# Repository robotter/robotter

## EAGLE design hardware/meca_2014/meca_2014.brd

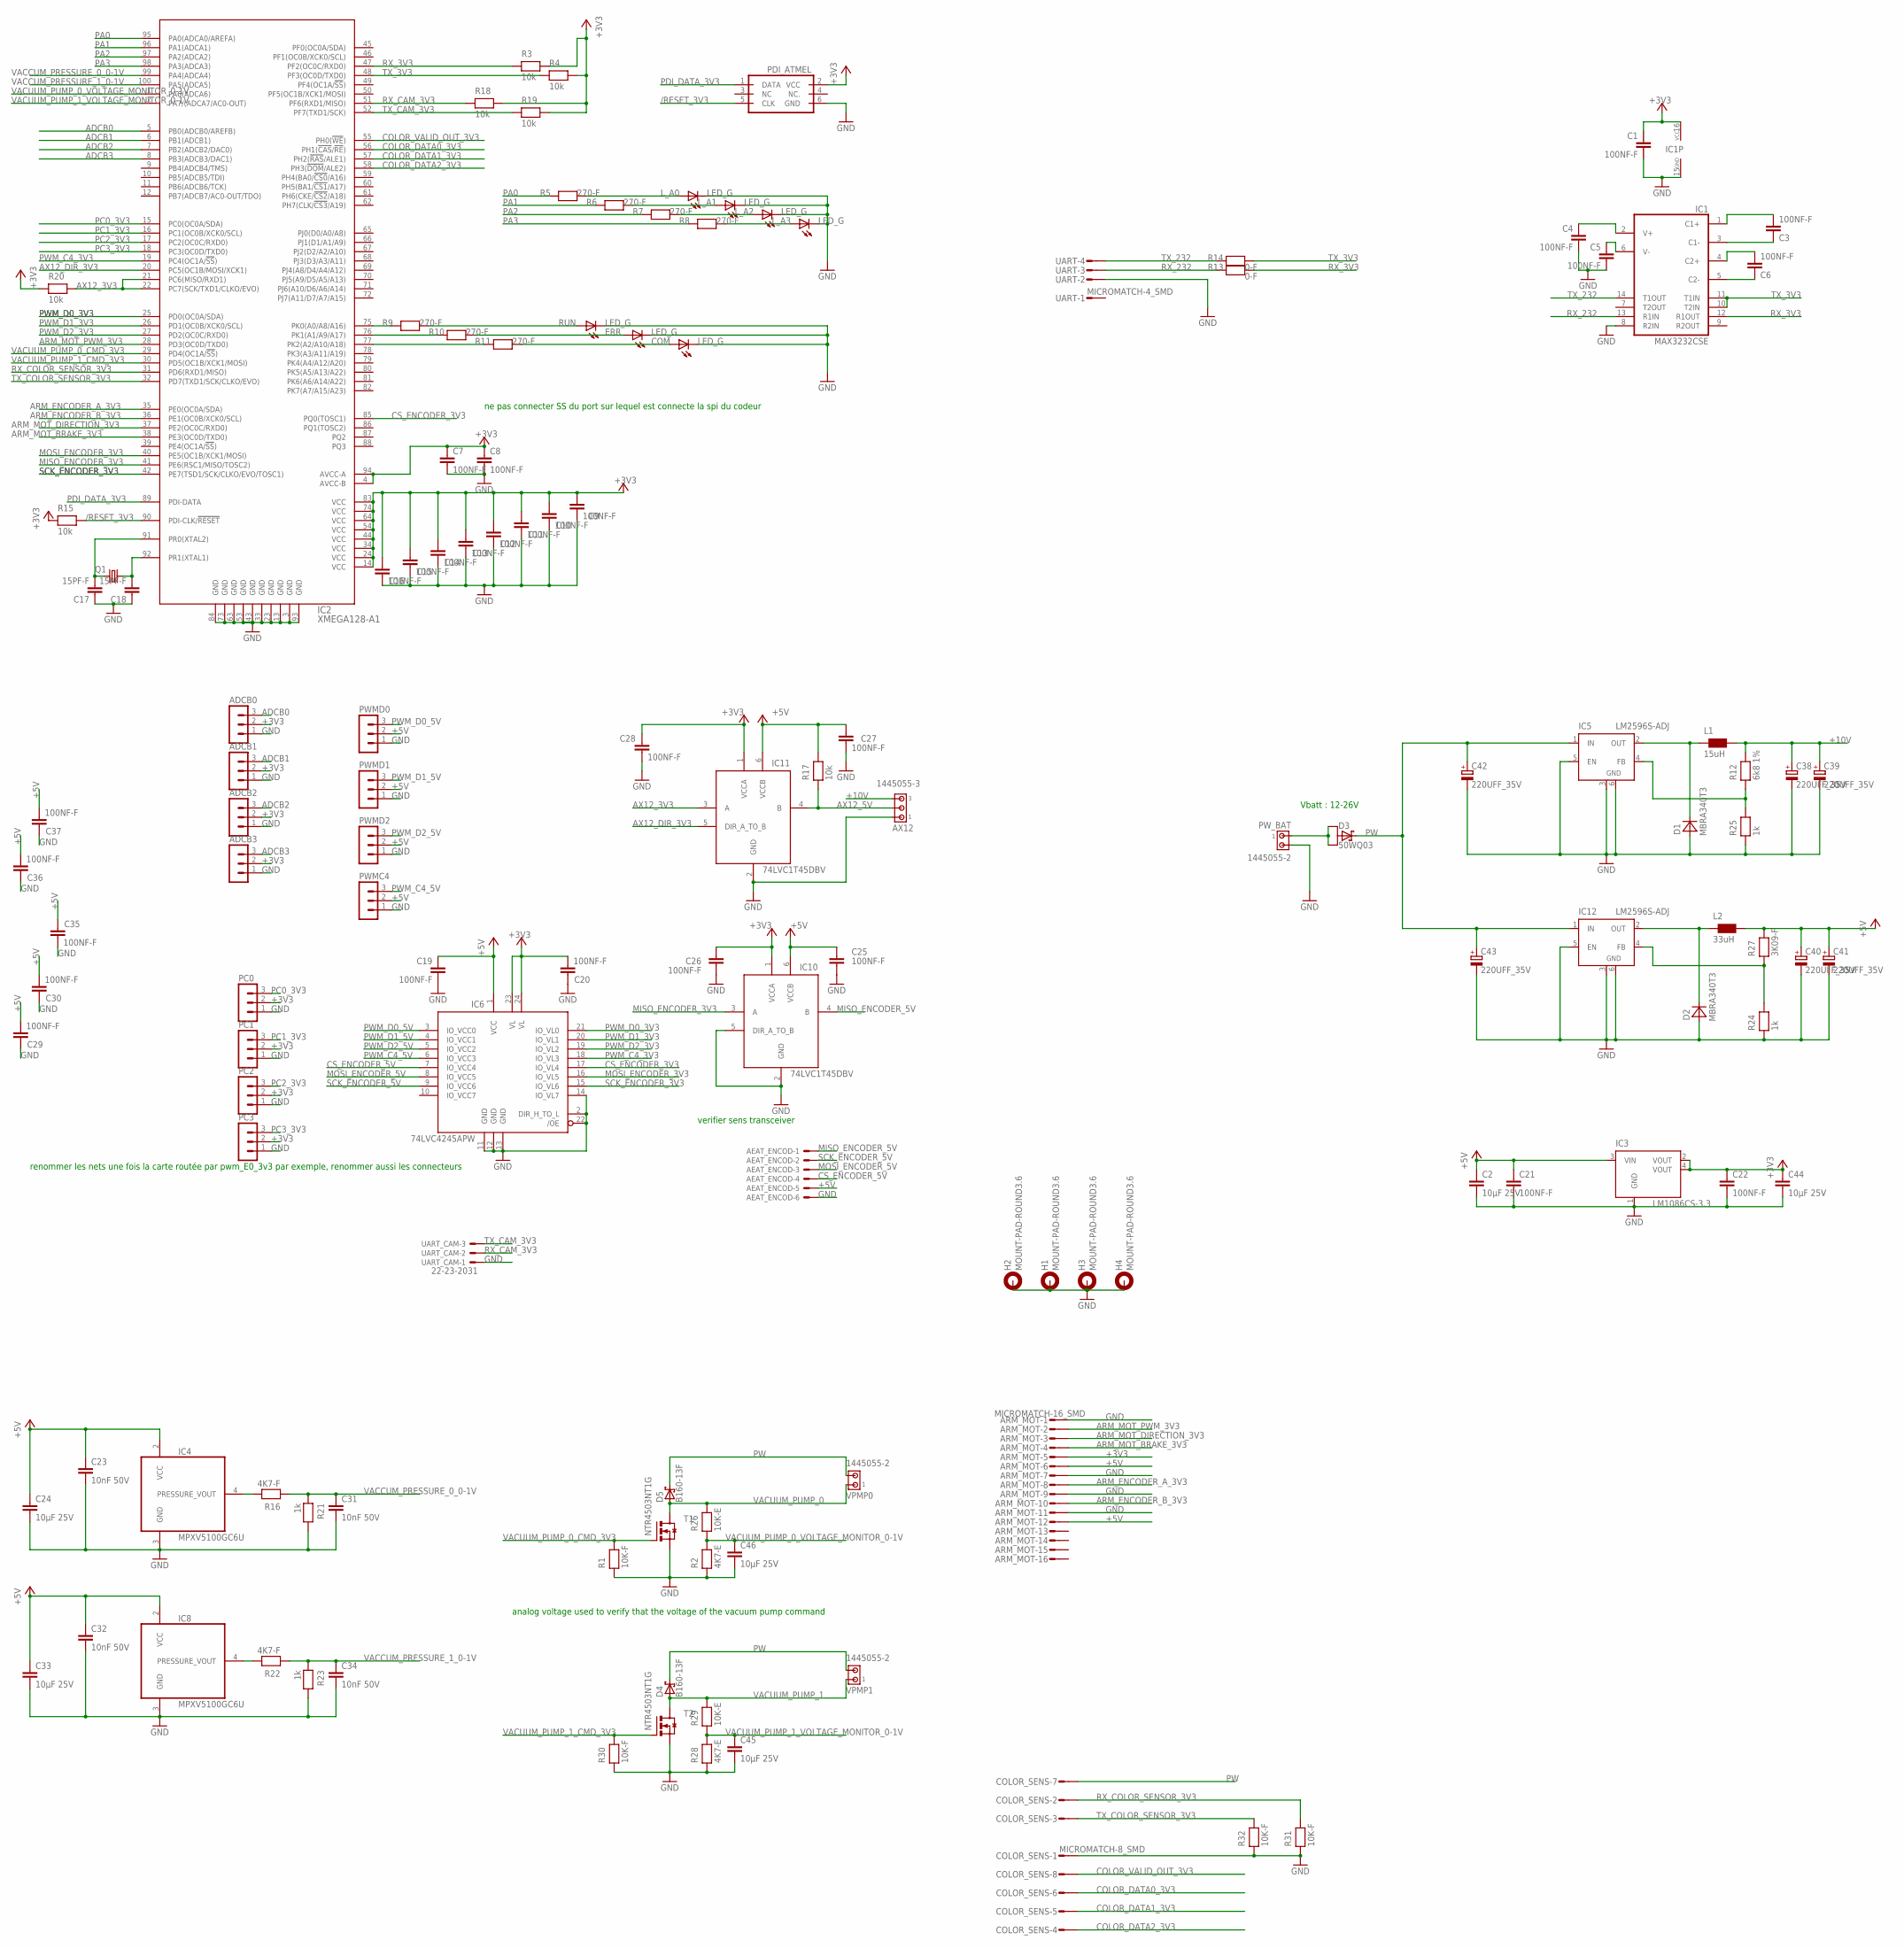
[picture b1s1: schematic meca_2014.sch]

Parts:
ADCB0, ADCB1, ADCB2, ADCB3: MA03-1
AEAT_ENCOD: 22-23-2061
ARM_MOT: MICROMATCH-16_SMD
AX12: 1445055-3
C1, C3, C4, C5, C6, C7, C8, C9, C10, C11, C12, C13, C14, C15, C16, C19, C20, C21, C22, C25, C26, C27, C28, C29, C30, C35, C36, C37: 100NF-F; C0603
C2, C24, C33, C44, C45, C46: 10µF 25V; C1210
C17, C18: 15PF-F; C0603
C23, C31, C32, C34: 10nF 50V; C0603
C38, C39, C40, C41, C42, C43: 220UFF_35V; PANASONIC_F
COLOR_SENS: MICROMATCH-8_SMD
COM: LED_G; CHIP-LED0805
D1, D2: MBRA340T3; SMA
D3: 50WQ03; TO252
D4, D5: B160-13F; SMA
ERR: LED_G; CHIP-LED0805
H1, H2, H3, H4: MOUNT-PAD-ROUND3.6; 3,6-PAD
IC1: MAX3232CSE; SO16
IC2: XMEGA128-A1; TQFP100
IC3: LM1086CS-3.3; TO263
IC4, IC8: MPXV5100GC6U; 482A
IC5, IC12: LM2596S-ADJ; TO263-5
IC6: 74LVC4245APW; TSSOP24
IC10, IC11: 74LVC1T45DBV; SOT23-6
L1: 15uH; SRR1280
L2: 33uH; SRR1280
L_A0, L_A1, L_A2, L_A3: LED_G; CHIP-LED0805
PC0, PC1, PC2, PC3: MA03-1
PDI_ATMEL: PDI_ATMELL; ML6L
PWMC4: MA03-1
PWMD0, PWMD1, PWMD2: MA03-1
PW_BAT: 1445055-2
Q1: CRYSTAL_16MHZ_HC49UP; HC49UP
R1, R30, R31, R32: 10K-F; R0603
R2, R28: 4K7-E; R0805
R3, R4, R15, R17, R18, R19, R20: 10k; R0603
R5, R6, R7, R8, R9, R10, R11: 270-F; R0603
R12: 6k8 1%; R0603
R13, R14: 0-F; R0603
R16, R22: 4K7-F; R0603
R21, R23, R24, R25: 1k; R0603
R26, R29: 10K-E; R0805
R27: 3K09-F; R0603
RUN: LED_G; CHIP-LED0805
T1, T2: NTR4503NT1G; SOT23
UART: MICROMATCH-4_SMD
UART_CAM: 22-23-2031
VPMP0, VPMP1: 1445055-2

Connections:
+3V3: ADCB0.2, ADCB1.2, ADCB2.2, ADCB3.2, ARM_MOT.5, C1.1, C7.1, C8.1, C9.1, C10.1, C11.1, C12.1, C13.1, C14.1, C15.1, C16.1, C20.1, C22.1, C26.1, C28.1, C44.1, IC1.16 (VCC), IC2.4 (AVCC-B), IC2.14 (VCC), IC2.24 (VCC), IC2.34 (VCC), IC2.44 (VCC), IC2.54 (VCC), IC2.64 (VCC), IC2.74 (VCC), IC2.83 (VCC), IC2.94 (AVCC-A), IC3.2 (VOUT), IC3.4 (VOUT), IC6.23 (VL), IC6.24 (VL), IC10.1 (VCCA), IC11.1 (VCCA), PC0.2, PC1.2, PC2.2, PC3.2, PDI_ATMEL.2 (VCC), R3.2, R4.2, R15.1, R18.2, R19.2, R20.1
+5V: AEAT_ENCOD.5, ARM_MOT.6, ARM_MOT.12, C2.1, C19.1, C21.1, C23.1, C24.1, C25.1, C27.1, C29.1, C30.1, C32.1, C33.1, C35.1, C36.1, C37.1, C40.+, C41.+, IC3.3 (VIN), IC4.2 (VCC), IC6.1 (VCC), IC8.2 (VCC), IC10.6 (VCCB), IC11.6 (VCCB), L2.2, PWMC4.2, PWMD0.2, PWMD1.2, PWMD2.2, R17.2, R27.2
+10V: AX12.3, C38.+, C39.+, L1.2, R12.2
/RESET_3V3: IC2.90 (PDI-CLK/!RESET), PDI_ATMEL.5 (CLK), R15.2
ADCB0: ADCB0.3, IC2.5 (PB0(ADCB0/AREFB))
ADCB1: ADCB1.3, IC2.6 (PB1(ADCB1))
ADCB2: ADCB2.3, IC2.7 (PB2(ADCB2/DAC0))
ADCB3: ADCB3.3, IC2.8 (PB3(ADCB3/DAC1))
ARM_ENCODER_A_3V3: ARM_MOT.8, IC2.35 (PE0(OC0A/SDA))
ARM_ENCODER_B_3V3: ARM_MOT.10, IC2.36 (PE1(OC0B/XCK0/SCL))
ARM_MOT_BRAKE_3V3: ARM_MOT.4, IC2.38 (PE3(OC0D/TXD0))
ARM_MOT_DIRECTION_3V3: ARM_MOT.3, IC2.37 (PE2(OC0C/RXD0))
ARM_MOT_PWM_3V3: ARM_MOT.2, IC2.28 (PD3(OC0D/TXD0))
AX12_3V3: IC2.21 (PC6(MISO/RXD1)), IC2.22 (PC7(SCK/TXD1/CLKO/EVO)), IC11.3 (A), R20.2
AX12_5V: AX12.2, IC11.4 (B), R17.1
AX12_DIR_3V3: IC2.20 (PC5(OC1B/MOSI/XCK1)), IC11.5 (DIR_A_TO_B)
COLOR_DATA0_3V3: COLOR_SENS.6, IC2.56 (PH1(!CAS!/!RE!))
COLOR_DATA1_3V3: COLOR_SENS.5, IC2.57 (PH2(!RAS!/ALE1))
COLOR_DATA2_3V3: COLOR_SENS.4, IC2.58 (PH3(!DOM!/ALE2))
COLOR_VALID_OUT_3V3: COLOR_SENS.8, IC2.55 (PH0(!WE!))
CS_ENCODER_3V3: IC2.85 (PQ0(TOSC1)), IC6.17 (IO_VL4)
CS_ENCODER_5V: AEAT_ENCOD.4, IC6.7 (IO_VCC4)
GND: ADCB0.1, ADCB1.1, ADCB2.1, ADCB3.1, AEAT_ENCOD.6, ARM_MOT.1, ARM_MOT.7, ARM_MOT.9, ARM_MOT.11, AX12.1, C1.2, C2.2, C4.2, C5.2, C7.2, C8.2, C9.2, C10.2, C11.2, C12.2, C13.2, C14.2, C15.2, C16.2, C17.1, C18.1, C19.2, C20.2, C21.2, C22.2, C23.2, C24.2, C25.2, C26.2, C27.2, C28.2, C29.2, C30.2, C31.2, C32.2, C33.2, C34.2, C35.2, C36.2, C37.2, C38.-, C39.-, C40.-, C41.-, C42.-, C43.-, C44.2, C45.2, C46.2, COLOR_SENS.1, COM.C, D1.A, D2.A, ERR.C, H1.B3,6, H2.B3,6, H3.B3,6, H4.B3,6, IC1.8 (R2IN), IC1.15 (GND), IC2.3 (GND), IC2.13 (GND), IC2.23 (GND), IC2.33 (GND), IC2.43 (GND), IC2.53 (GND), IC2.63 (GND), IC2.73 (GND), IC2.84 (GND), IC2.93 (GND), IC3.1 (GND), IC4.3 (GND), IC5.3 (GND), IC5.5 (EN), IC5.6 (GND), IC6.2 (DIR_H_TO_L), IC6.11 (GND), IC6.12 (GND), IC6.13 (GND), IC6.14 (IO_VL7), IC6.22 (/OE), IC8.3 (GND), IC10.2 (GND), IC10.5 (DIR_A_TO_B), IC11.2 (GND), IC12.3 (GND), IC12.5 (EN), IC12.6 (GND), L_A0.C, L_A1.C, L_A2.C, L_A3.C, PC0.1, PC1.1, PC2.1, PC3.1, PDI_ATMEL.6 (GND), PWMC4.1, PWMD0.1, PWMD1.1, PWMD2.1, PW_BAT.2, R1.1, R2.1, R21.2, R23.2, R24.1, R25.1, R28.1, R30.1, R31.1, R32.1, RUN.C, T1.2 (S), T2.2 (S), UART.2, UART_CAM.1
MISO_ENCODER_3V3: IC2.41 (PE6(RSC1/MISO/TOSC2)), IC10.3 (A)
MISO_ENCODER_5V: AEAT_ENCOD.1, IC10.4 (B)
MOSI_ENCODER_3V3: IC2.40 (PE5(OC1B/XCK1/MOSI)), IC6.16 (IO_VL5)
MOSI_ENCODER_5V: AEAT_ENCOD.3, IC6.8 (IO_VCC5)
unnamed: C3.1, IC1.1 (C1+)
unnamed: R9.2, RUN.A
unnamed: IC12.4 (FB), R24.2, R27.1
unnamed: ERR.A, R10.2
unnamed: C3.2, IC1.3 (C1-)
unnamed: C6.1, IC1.4 (C2+)
unnamed: COM.A, R11.2
unnamed: IC5.4 (FB), R12.1, R25.2
unnamed: IC2.75 (PK0(A0/A8/A16)), R9.1
unnamed: IC2.76 (PK1(A1/A9/A17)), R10.1
unnamed: C4.1, IC1.2 (V+)
unnamed: IC2.77 (PK2(A2/A10/A18)), R11.1
unnamed: C5.1, IC1.6 (V-)
unnamed: D3.1 (A1), D3.3 (A2), PW_BAT.1
unnamed: IC4.4 (PRESSURE_VOUT), R16.2
unnamed: D1.C, IC5.2 (OUT), L1.1
unnamed: D2.C, IC12.2 (OUT), L2.1
unnamed: IC8.4 (PRESSURE_VOUT), R22.2
unnamed: C6.2, IC1.5 (C2-)
unnamed: C17.2, IC2.91 (PR0(XTAL2)), Q1.2
unnamed: C18.2, IC2.92 (PR1(XTAL1)), Q1.1
unnamed: L_A0.A, R5.2
unnamed: L_A1.A, R6.2
unnamed: L_A2.A, R7.2
unnamed: L_A3.A, R8.2
PA0: IC2.95 (PA0(ADCA0/AREFA)), R5.1
PA1: IC2.96 (PA1(ADCA1)), R6.1
PA2: IC2.97 (PA2(ADCA2)), R7.1
PA3: IC2.98 (PA3(ADCA3)), R8.1
PC0_3V3: IC2.15 (PC0(OC0A/SDA)), PC0.3
PC1_3V3: IC2.16 (PC1(OC0B/XCK0/SCL)), PC1.3
PC2_3V3: IC2.17 (PC2(OC0C/RXD0)), PC2.3
PC3_3V3: IC2.18 (PC3(OC0D/TXD0)), PC3.3
PDI_DATA_3V3: IC2.89 (PDI-DATA), PDI_ATMEL.1 (DATA)
PW: C42.+, C43.+, COLOR_SENS.7, D3.4 (C), D4.A (C), D5.A (C), IC5.1 (IN), IC12.1 (IN), VPMP0.2, VPMP1.2
PWM_C4_3V3: IC2.19 (PC4(OC1A/!SS!)), IC6.18 (IO_VL3)
PWM_C4_5V: IC6.6 (IO_VCC3), PWMC4.3
PWM_D0_3V3: IC2.25 (PD0(OC0A/SDA)), IC6.21 (IO_VL0)
PWM_D0_5V: IC6.3 (IO_VCC0), PWMD0.3
PWM_D1_3V3: IC2.26 (PD1(OC0B/XCK0/SCL)), IC6.20 (IO_VL1)
PWM_D1_5V: IC6.4 (IO_VCC1), PWMD1.3
PWM_D2_3V3: IC2.27 (PD2(OC0C/RXD0)), IC6.19 (IO_VL2)
PWM_D2_5V: IC6.5 (IO_VCC2), PWMD2.3
RX_3V3: IC1.12 (R1OUT), IC2.47 (PF2(OC0C/RXD0)), R3.1, R13.2
RX_232: IC1.13 (R1IN), R13.1, UART.3
RX_CAM_3V3: IC2.51 (PF6(RXD1/MISO)), R18.1, UART_CAM.2
RX_COLOR_SENSOR_3V3: COLOR_SENS.2, IC2.31 (PD6(RXD1/MISO)), R31.2
SCK_ENCODER_3V3: IC2.42 (PE7(TSD1/SCK/CLKO/EVO/TOSC1)), IC6.15 (IO_VL6)
SCK_ENCODER_5V: AEAT_ENCOD.2, IC6.9 (IO_VCC6)
TX_3V3: IC1.10 (T2IN), IC1.11 (T1IN), IC2.48 (PF3(OC0D/TXD0)), R4.1, R14.2
TX_232: IC1.14 (T1OUT), R14.1, UART.4
TX_CAM_3V3: IC2.52 (PF7(TXD1/SCK)), R19.1, UART_CAM.3
TX_COLOR_SENSOR_3V3: COLOR_SENS.3, IC2.32 (PD7(TXD1/SCK/CLKO/EVO)), R32.2
VACCUM_PRESSURE_0_0-1V: C31.1, IC2.99 (PA4(ADCA4)), R16.1, R21.1
VACCUM_PRESSURE_1_0-1V: C34.1, IC2.100 (PA5(ADCA5)), R22.1, R23.1
VACUUM_PUMP_0: D5.C (A), R26.2, T1.3 (D), VPMP0.1
VACUUM_PUMP_0_CMD_3V3: IC2.29 (PD4(OC1A/!SS!)), R1.2, T1.1 (G)
VACUUM_PUMP_0_VOLTAGE_MONITOR_0-1V: C46.1, IC2.1 (PA6(ADCA6)), R2.2, R26.1
VACUUM_PUMP_1: D4.C (A), R29.2, T2.3 (D), VPMP1.1
VACUUM_PUMP_1_CMD_3V3: IC2.30 (PD5(OC1B/XCK1/MOSI)), R30.2, T2.1 (G)
VACUUM_PUMP_1_VOLTAGE_MONITOR_0-1V: C45.1, IC2.2 (PA7/(ADCA7/AC0-OUT)), R28.2, R29.1

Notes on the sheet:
Vbatt : 12-26V
analog voltage used to verify that the voltage of the vacuum pump command
renommer les nets une fois la carte routée par pwm_E0_3v3 par exemple, renommer aussi les connecteurs
verifier sens transceiver
ne pas connecter SS du port sur lequel est connecte la spi du codeur

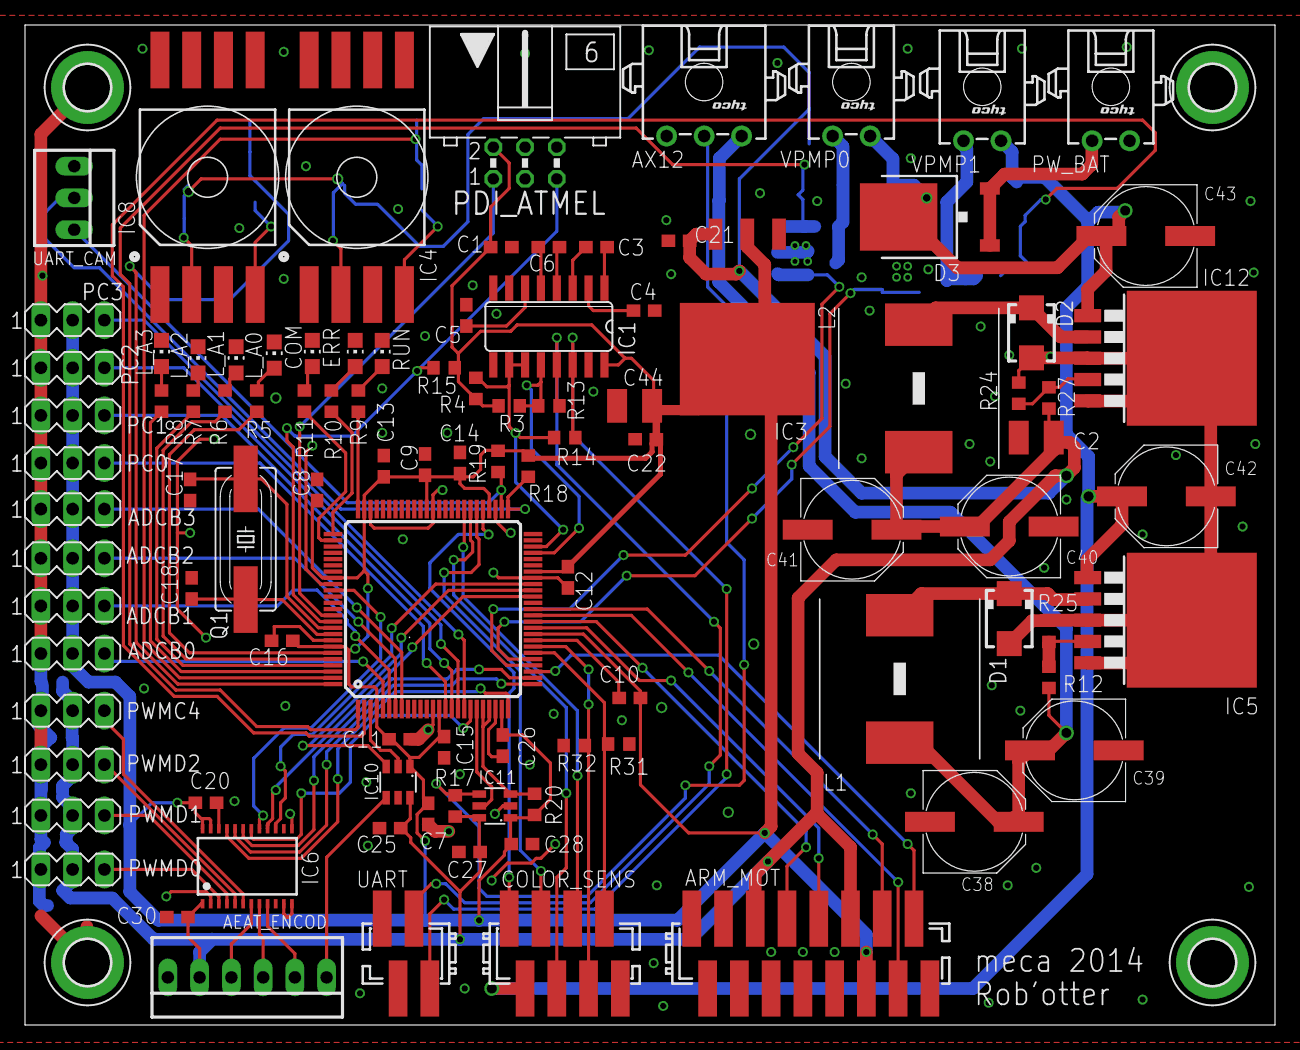
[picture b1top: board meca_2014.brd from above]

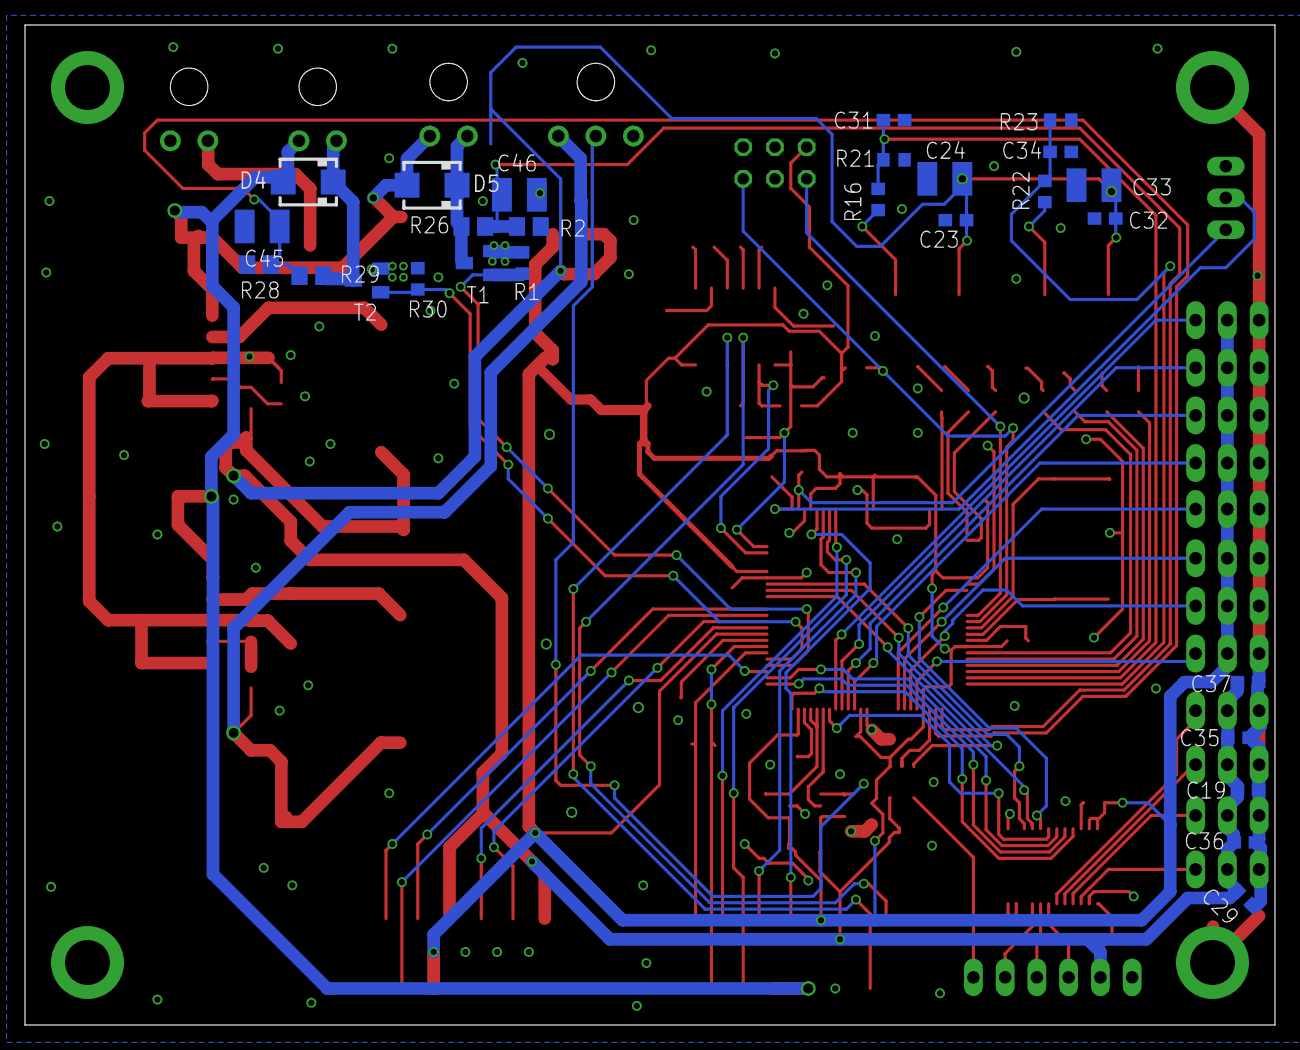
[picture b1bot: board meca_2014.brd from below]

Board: 2 copper layers, 100.0 x 80.0 mm, 131 parts (27 on the bottom side), 88 nets.

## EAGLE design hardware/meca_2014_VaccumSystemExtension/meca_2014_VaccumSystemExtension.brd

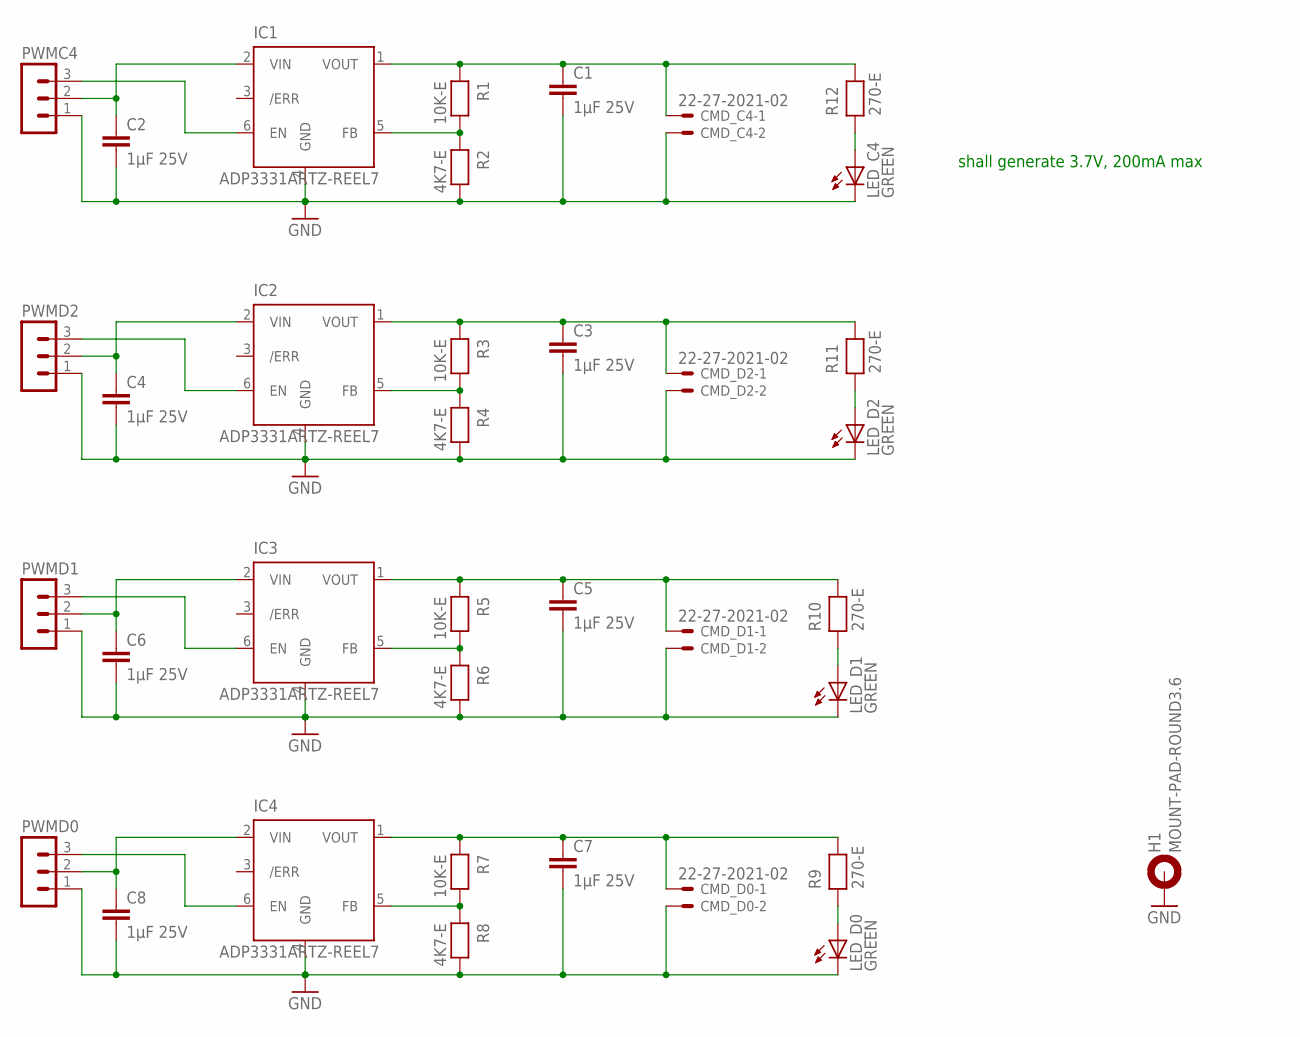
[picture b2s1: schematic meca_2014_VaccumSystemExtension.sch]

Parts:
C1, C2, C3, C4, C5, C6, C7, C8: 1µF 25V; C1206
CMD_C4: 22-27-2021-02; 6410-02
CMD_D0, CMD_D1, CMD_D2: 22-27-2021-02; 6410-02
H1: MOUNT-PAD-ROUND3.6; 3,6-PAD
IC1, IC2, IC3, IC4: ADP3331ARTZ-REEL7; SOT23-6
LED_C4: GREEN; CHIP-LED0805
LED_D0, LED_D1, LED_D2: GREEN; CHIP-LED0805
PWMC4: MA03-1
PWMD0, PWMD1, PWMD2: MA03-1
R1, R3, R5, R7: 10K-E; R0805
R2, R4, R6, R8: 4K7-E; R0805
R9, R10, R11, R12: 270-E; R0805

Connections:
5V_C4: C2.1, IC1.2 (VIN), PWMC4.2
5V_D0: C8.1, IC4.2 (VIN), PWMD0.2
5V_D1: C6.1, IC3.2 (VIN), PWMD1.2
5V_D2: C4.1, IC2.2 (VIN), PWMD2.2
GND: C1.2, C2.2, C3.2, C4.2, C5.2, C6.2, C7.2, C8.2, CMD_C4.2, CMD_D0.2, CMD_D1.2, CMD_D2.2, H1.B3,6, IC1.4 (GND), IC2.4 (GND), IC3.4 (GND), IC4.4 (GND), LED_C4.C, LED_D0.C, LED_D1.C, LED_D2.C, PWMC4.1, PWMD0.1, PWMD1.1, PWMD2.1, R2.2, R4.2, R6.2, R8.2
unnamed: IC1.5 (FB), R1.2, R2.1
unnamed: IC2.5 (FB), R3.2, R4.1
unnamed: C1.1, CMD_C4.1, IC1.1 (VOUT), R1.1, R12.2
unnamed: LED_D0.A, R9.1
unnamed: LED_D1.A, R10.1
unnamed: C3.1, CMD_D2.1, IC2.1 (VOUT), R3.1, R11.2
unnamed: LED_C4.A, R12.1
unnamed: LED_D2.A, R11.1
unnamed: IC3.5 (FB), R5.2, R6.1
unnamed: C5.1, CMD_D1.1, IC3.1 (VOUT), R5.1, R10.2
unnamed: IC4.5 (FB), R7.2, R8.1
unnamed: C7.1, CMD_D0.1, IC4.1 (VOUT), R7.1, R9.2
PWM_C4_5V: IC1.6 (EN), PWMC4.3
PWM_D0_5V: IC4.6 (EN), PWMD0.3
PWM_D1_5V: IC3.6 (EN), PWMD1.3
PWM_D2_5V: IC2.6 (EN), PWMD2.3

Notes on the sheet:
shall generate 3.7V, 200mA max

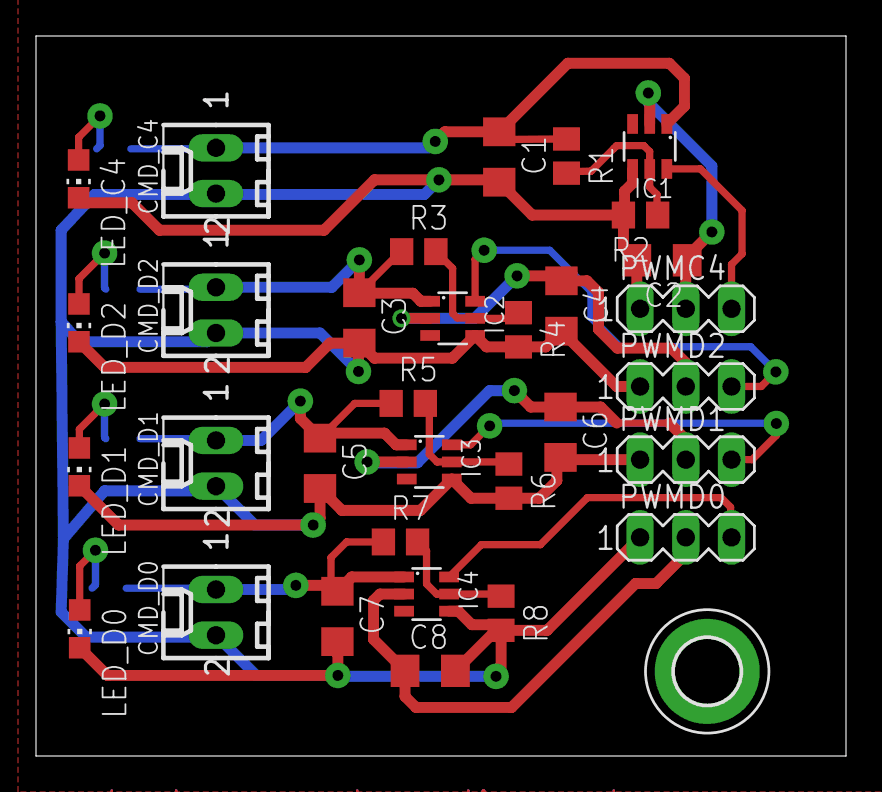
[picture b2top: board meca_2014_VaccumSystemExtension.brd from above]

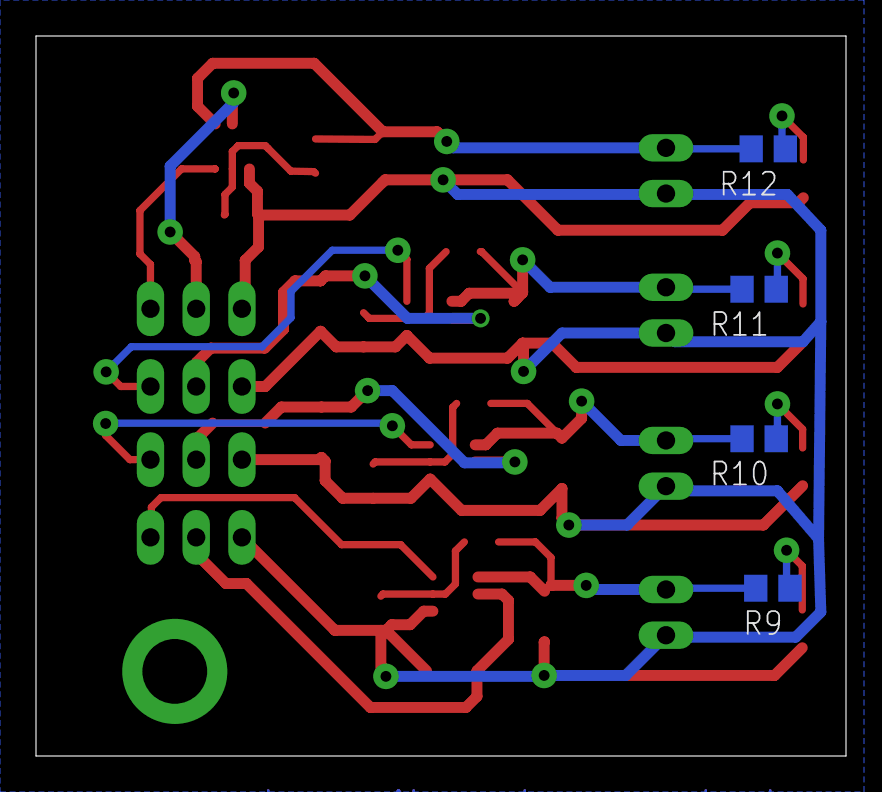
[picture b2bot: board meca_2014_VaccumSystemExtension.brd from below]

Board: 2 copper layers, 45.0 x 40.0 mm, 37 parts (4 on the bottom side), 21 nets.

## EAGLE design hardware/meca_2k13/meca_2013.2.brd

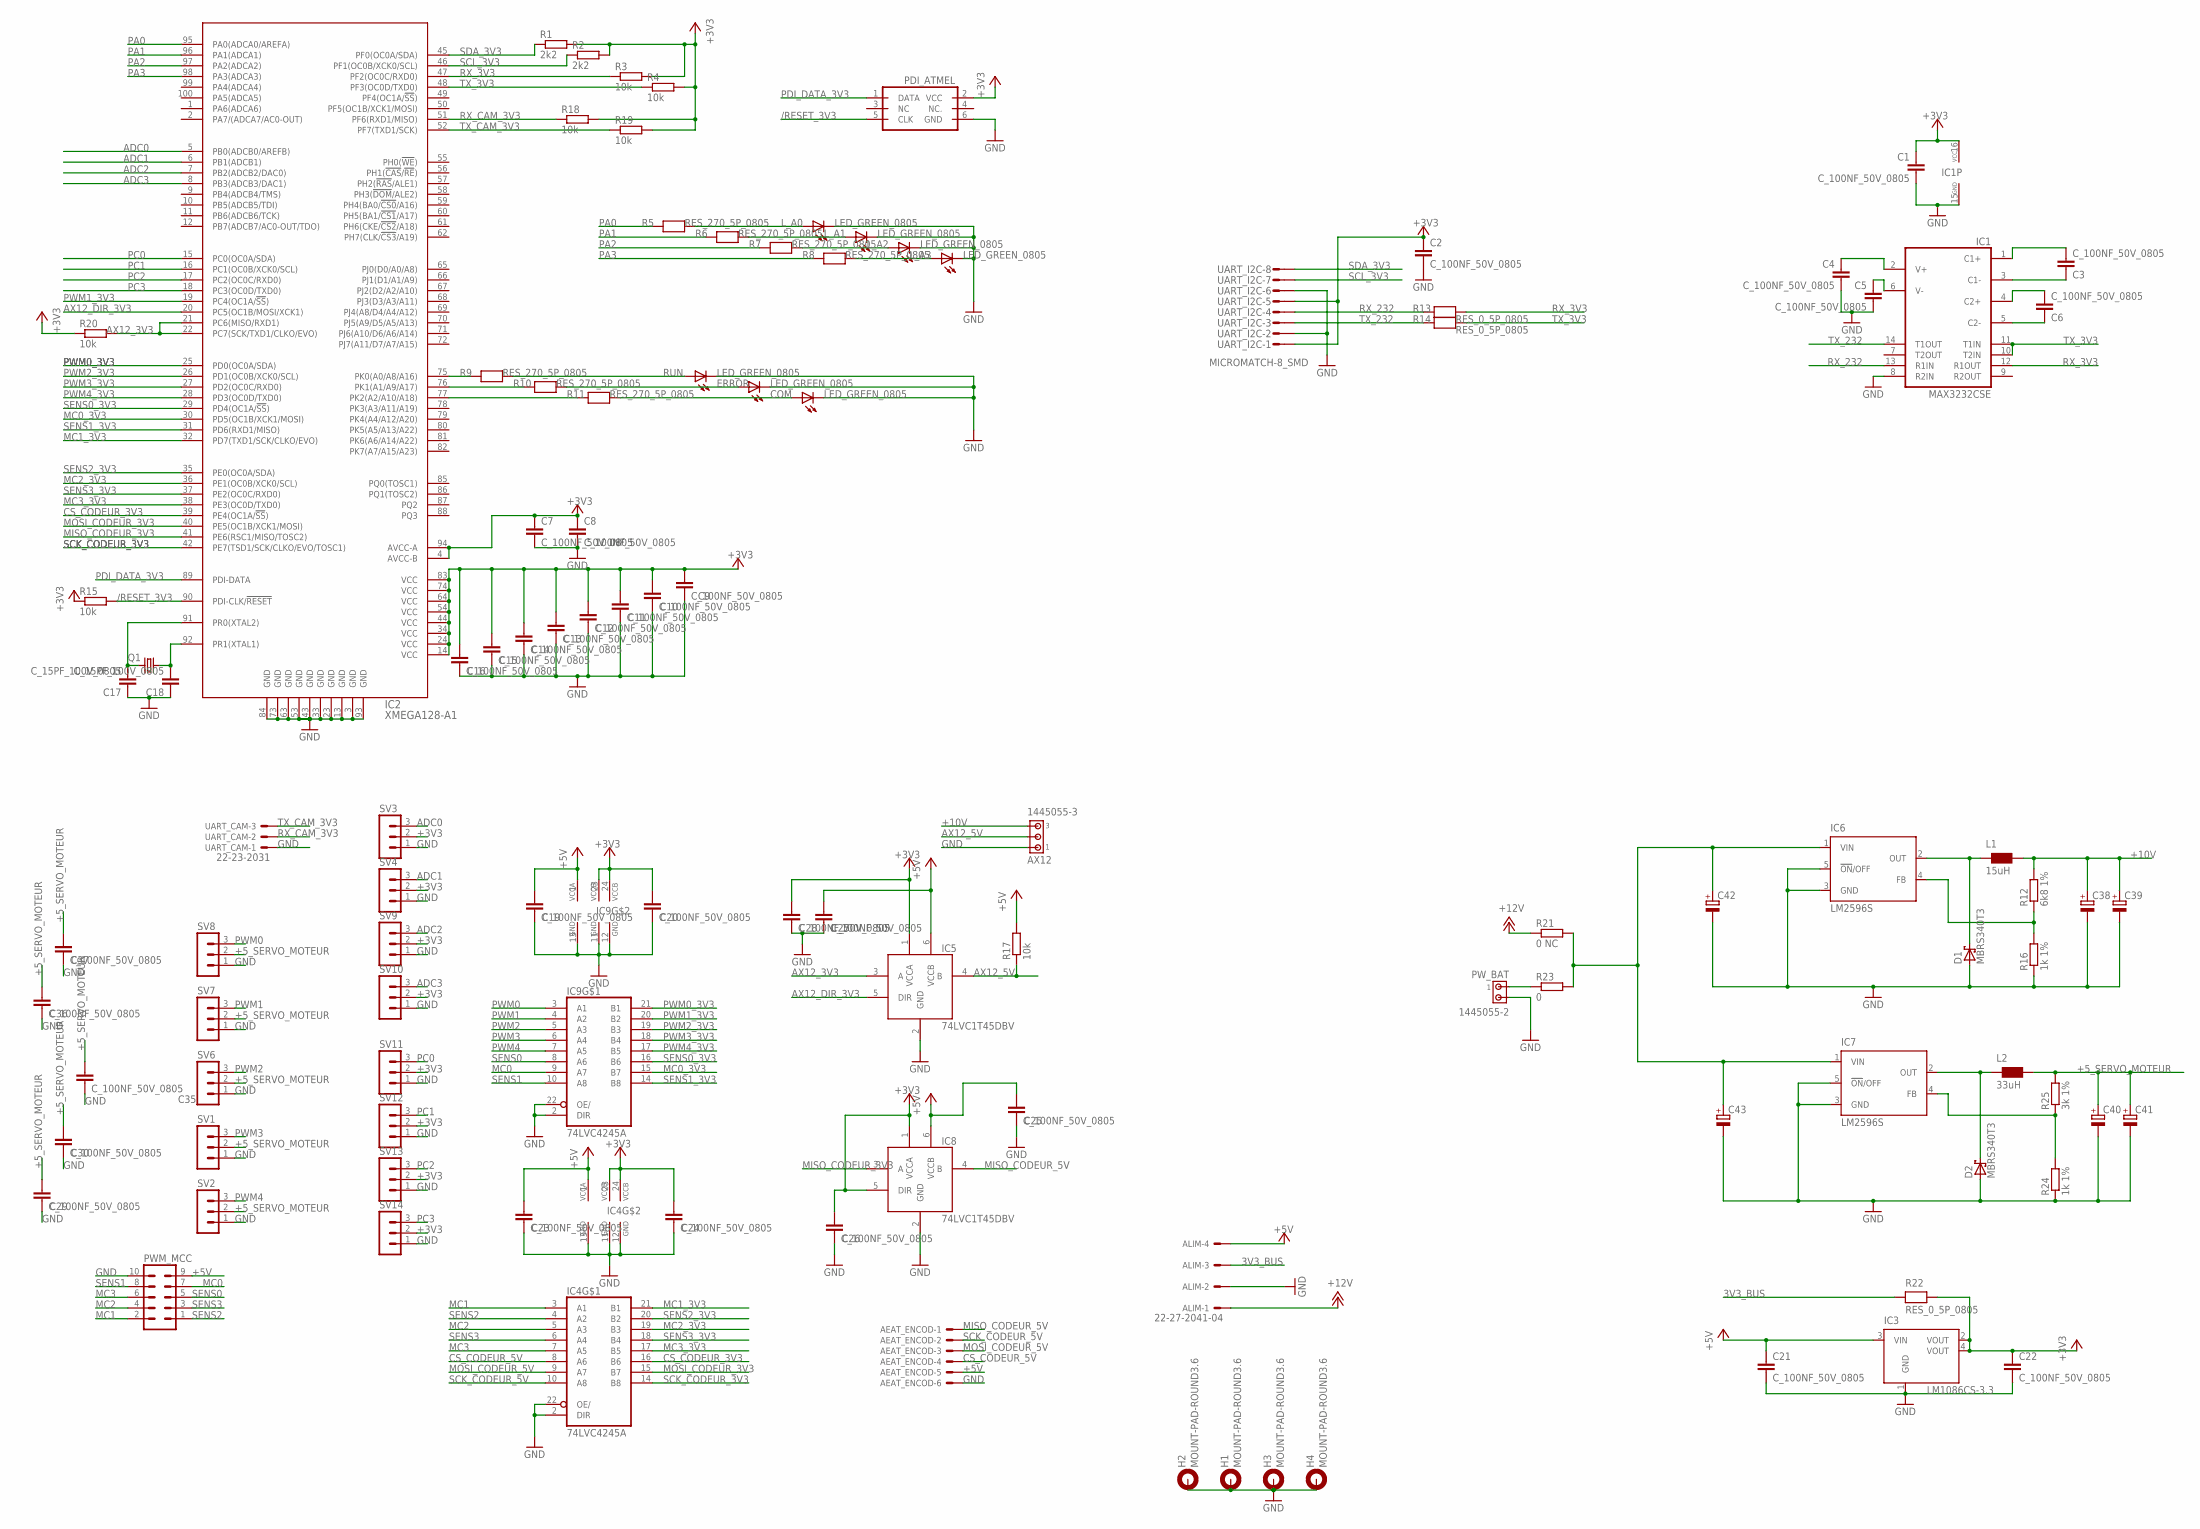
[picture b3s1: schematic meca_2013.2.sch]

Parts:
AEAT_ENCOD: 22-23-2061
ALIM: 22-27-2041-04; 6410-04
AX12: 1445055-3
C1, C2, C3, C4, C5, C6, C7, C8, C9, C10, C11, C12, C13, C14, C15, C16, C19, C20, C21, C22, C23, C24, C25, C26, C27, C28, C29, C30, C35, C36, C37: C_100NF_50V_0805; C0805
C17, C18: C_15PF_100V_0805; C0805
C38, C39, C40, C41, C42, C43: CPOL-EUG; PANASONIC_G
COM: LED_GREEN_0805; CHIP-LED0805
D1, D2: MBRS340T3; SMC
ERROR: LED_GREEN_0805; CHIP-LED0805
H1, H2, H3, H4: MOUNT-PAD-ROUND3.6; 3,6-PAD
IC1: MAX3232CSE; SO16
IC2: XMEGA128-A1; TQFP100
IC3: LM1086CS-3.3; TO263
IC4, IC9: 74LVC4245A; TSSOP28
IC5, IC8: 74LVC1T45DBV; SOT23-6
IC6, IC7: LM2596S; TO263-5
L1: 15uH; WE-PD_L/XL/XXL
L2: 33uH; WE-PD_L/XL/XXL
L_A0, L_A1, L_A2, L_A3: LED_GREEN_0805; CHIP-LED0805
PDI_ATMEL: PDI_ATMEL; ML6
PWM_MCC: ML10
PW_BAT: 1445055-2
Q1: CRYSTAL_16MHZ_HC49UP; HC49UP
R1, R2: 2k2; R0603
R3, R4, R15, R18, R19, R20: 10k; R0603
R5, R6, R7, R8, R9, R10, R11: RES_270_5P_0805; R0805
R12: 6k8 1%; R0805
R13, R14, R22: RES_0_5P_0805; R0805
R16, R24: 1k 1%; R0805
R17: 10k; R0805
R21: 0 NC; R0805
R23: 0; R0805
R25: 3k 1%; R0805
RUN: LED_GREEN_0805; CHIP-LED0805
SV1, SV2, SV3, SV4, SV6, SV7, SV8, SV9, SV10, SV11, SV12, SV13, SV14: MA03-1
UART_CAM: 22-23-2031
UART_I2C: MICROMATCH-8_SMD

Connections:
3V3_BUS: ALIM.3, R22.1
+3V3: C1.1, C2.1, C7.1, C8.1, C9.1, C10.1, C11.1, C12.1, C13.1, C14.1, C15.1, C16.1, C20.1, C22.1, C24.1, C26.1, C28.1, IC1.16 (VCC), IC2.4 (AVCC-B), IC2.14 (VCC), IC2.24 (VCC), IC2.34 (VCC), IC2.44 (VCC), IC2.54 (VCC), IC2.64 (VCC), IC2.74 (VCC), IC2.83 (VCC), IC2.94 (AVCC-A), IC3.2 (VOUT), IC3.4 (VOUT), IC4.23 (VCCB), IC4.24 (VCCB), IC5.1 (VCCA), IC8.1 (VCCA), IC8.5 (DIR), IC9.23 (VCCB), IC9.24 (VCCB), PDI_ATMEL.2 (VCC), R1.2, R2.2, R3.2, R4.2, R15.1, R18.2, R19.2, R20.1, R22.2, SV3.2, SV4.2, SV9.2, SV10.2, SV11.2, SV12.2, SV13.2, SV14.2, UART_I2C.1, UART_I2C.5
+5V: AEAT_ENCOD.5, ALIM.4, C19.1, C21.1, C23.1, C25.1, C27.1, IC3.3 (VIN), IC4.1 (VCCA), IC5.6 (VCCB), IC8.6 (VCCB), IC9.1 (VCCA), PWM_MCC.9, R17.2
+5_SERVO_MOTEUR: C29.1, C30.1, C35.1, C36.1, C37.1, C40.+, C41.+, L2.1 (2), R25.2, SV1.2, SV2.2, SV6.2, SV7.2, SV8.2
+10V: AX12.3, C38.+, C39.+, L1.1 (2), R12.2
+12V: ALIM.1, R21.1
/RESET_3V3: IC2.90 (PDI-CLK/!RESET), PDI_ATMEL.5 (CLK), R15.2
ADC0: IC2.5 (PB0(ADCB0/AREFB)), SV3.3
ADC1: IC2.6 (PB1(ADCB1)), SV4.3
ADC2: IC2.7 (PB2(ADCB2/DAC0)), SV9.3
ADC3: IC2.8 (PB3(ADCB3/DAC1)), SV10.3
AX12_3V3: IC2.21 (PC6(MISO/RXD1)), IC2.22 (PC7(SCK/TXD1/CLKO/EVO)), IC5.3 (A), R20.2
AX12_5V: AX12.2, IC5.4 (B), R17.1
AX12_DIR_3V3: IC2.20 (PC5(OC1B/MOSI/XCK1)), IC5.5 (DIR)
CS_CODEUR_3V3: IC2.39 (PE4(OC1A/!SS!)), IC4.16 (B6)
CS_CODEUR_5V: AEAT_ENCOD.4, IC4.8 (A6)
GND: AEAT_ENCOD.6, ALIM.2, AX12.1, C1.2, C2.2, C4.2, C5.2, C7.2, C8.2, C9.2, C10.2, C11.2, C12.2, C13.2, C14.2, C15.2, C16.2, C17.1, C18.1, C19.2, C20.2, C21.2, C22.2, C23.2, C24.2, C25.2, C26.2, C27.2, C28.2, C29.2, C30.2, C35.2, C36.2, C37.2, C38.-, C39.-, C40.-, C41.-, C42.-, C43.-, COM.C, D1.A, D2.A, ERROR.C, H1.B3,6, H2.B3,6, H3.B3,6, H4.B3,6, IC1.8 (R2IN), IC1.15 (GND), IC2.3 (GND), IC2.13 (GND), IC2.23 (GND), IC2.33 (GND), IC2.43 (GND), IC2.53 (GND), IC2.63 (GND), IC2.73 (GND), IC2.84 (GND), IC2.93 (GND), IC3.1 (GND), IC4.2 (DIR), IC4.11 (GND), IC4.12 (GND), IC4.13 (GND), IC4.22 (OE/), IC5.2 (GND), IC6.3 (GND), IC6.5 (!ON!/OFF), IC7.3 (GND), IC7.5 (!ON!/OFF), IC8.2 (GND), IC9.2 (DIR), IC9.11 (GND), IC9.12 (GND), IC9.13 (GND), IC9.22 (OE/), L_A0.C, L_A1.C, L_A2.C, L_A3.C, PDI_ATMEL.6 (GND), PWM_MCC.10, PW_BAT.2, R16.1, R24.1, RUN.C, SV1.1, SV2.1, SV3.1, SV4.1, SV6.1, SV7.1, SV8.1, SV9.1, SV10.1, SV11.1, SV12.1, SV13.1, SV14.1, UART_CAM.1, UART_I2C.2, UART_I2C.6
MC0: IC9.9 (A7), PWM_MCC.7
MC0_3V3: IC2.30 (PD5(OC1B/XCK1/MOSI)), IC9.15 (B7)
MC1: IC4.3 (A1), PWM_MCC.2
MC1_3V3: IC2.32 (PD7(TXD1/SCK/CLKO/EVO)), IC4.21 (B1)
MC2: IC4.5 (A3), PWM_MCC.4
MC2_3V3: IC2.36 (PE1(OC0B/XCK0/SCL)), IC4.19 (B3)
MC3: IC4.7 (A5), PWM_MCC.6
MC3_3V3: IC2.38 (PE3(OC0D/TXD0)), IC4.17 (B5)
MISO_CODEUR_3V3: IC2.41 (PE6(RSC1/MISO/TOSC2)), IC8.3 (A)
MISO_CODEUR_5V: AEAT_ENCOD.1, IC8.4 (B)
MOSI_CODEUR_3V3: IC2.40 (PE5(OC1B/XCK1/MOSI)), IC4.15 (B7)
MOSI_CODEUR_5V: AEAT_ENCOD.3, IC4.9 (A7)
unnamed: C3.1, IC1.1 (C1+)
unnamed: R9.2, RUN.A
unnamed: IC7.4 (FB), R24.2, R25.1
unnamed: ERROR.A, R10.2
unnamed: C3.2, IC1.3 (C1-)
unnamed: C6.1, IC1.4 (C2+)
unnamed: COM.A, R11.2
unnamed: IC6.4 (FB), R12.1, R16.2
unnamed: IC2.75 (PK0(A0/A8/A16)), R9.1
unnamed: IC2.76 (PK1(A1/A9/A17)), R10.1
unnamed: C4.1, IC1.2 (V+)
unnamed: IC2.77 (PK2(A2/A10/A18)), R11.1
unnamed: C5.1, IC1.6 (V-)
unnamed: PW_BAT.1, R23.1
unnamed: D1.C, IC6.2 (OUT), L1.2 (1)
unnamed: D2.C, IC7.2 (OUT), L2.2 (1)
unnamed: C6.2, IC1.5 (C2-)
unnamed: C17.2, IC2.91 (PR0(XTAL2)), Q1.2
unnamed: C18.2, IC2.92 (PR1(XTAL1)), Q1.1
unnamed: L_A0.A, R5.2
unnamed: L_A1.A, R6.2
unnamed: L_A2.A, R7.2
unnamed: L_A3.A, R8.2
PA0: IC2.95 (PA0(ADCA0/AREFA)), R5.1
PA1: IC2.96 (PA1(ADCA1)), R6.1
PA2: IC2.97 (PA2(ADCA2)), R7.1
PA3: IC2.98 (PA3(ADCA3)), R8.1
PC0: IC2.15 (PC0(OC0A/SDA)), SV11.3
PC1: IC2.16 (PC1(OC0B/XCK0/SCL)), SV12.3
PC2: IC2.17 (PC2(OC0C/RXD0)), SV13.3
PC3: IC2.18 (PC3(OC0D/TXD0)), SV14.3
PDI_DATA_3V3: IC2.89 (PDI-DATA), PDI_ATMEL.1 (DATA)
PW: C42.+, C43.+, IC6.1 (VIN), IC7.1 (VIN), R21.2, R23.2
PWM0: IC9.3 (A1), SV8.3
PWM0_3V3: IC2.25 (PD0(OC0A/SDA)), IC9.21 (B1)
PWM1: IC9.4 (A2), SV7.3
PWM1_3V3: IC2.19 (PC4(OC1A/!SS!)), IC9.20 (B2)
PWM2: IC9.5 (A3), SV6.3
PWM2_3V3: IC2.26 (PD1(OC0B/XCK0/SCL)), IC9.19 (B3)
PWM3: IC9.6 (A4), SV1.3
PWM3_3V3: IC2.27 (PD2(OC0C/RXD0)), IC9.18 (B4)
PWM4: IC9.7 (A5), SV2.3
PWM4_3V3: IC2.28 (PD3(OC0D/TXD0)), IC9.17 (B5)
RX_3V3: IC1.12 (R1OUT), IC2.47 (PF2(OC0C/RXD0)), R3.1, R13.2
RX_232: IC1.13 (R1IN), R13.1, UART_I2C.4
RX_CAM_3V3: IC2.51 (PF6(RXD1/MISO)), R18.1, UART_CAM.2
SCK_CODEUR_3V3: IC2.42 (PE7(TSD1/SCK/CLKO/EVO/TOSC1)), IC4.14 (B8)
SCK_CODEUR_5V: AEAT_ENCOD.2, IC4.10 (A8)
SCL_3V3: IC2.46 (PF1(OC0B/XCK0/SCL)), R2.1, UART_I2C.7
SDA_3V3: IC2.45 (PF0(OC0A/SDA)), R1.1, UART_I2C.8
SENS0: IC9.8 (A6), PWM_MCC.5
SENS0_3V3: IC2.29 (PD4(OC1A/!SS!)), IC9.16 (B6)
SENS1: IC9.10 (A8), PWM_MCC.8
SENS1_3V3: IC2.31 (PD6(RXD1/MISO)), IC9.14 (B8)
SENS2: IC4.4 (A2), PWM_MCC.1
SENS2_3V3: IC2.35 (PE0(OC0A/SDA)), IC4.20 (B2)
SENS3: IC4.6 (A4), PWM_MCC.3
SENS3_3V3: IC2.37 (PE2(OC0C/RXD0)), IC4.18 (B4)
TX_3V3: IC1.10 (T2IN), IC1.11 (T1IN), IC2.48 (PF3(OC0D/TXD0)), R4.1, R14.2
TX_232: IC1.14 (T1OUT), R14.1, UART_I2C.3
TX_CAM_3V3: IC2.52 (PF7(TXD1/SCK)), R19.1, UART_CAM.3

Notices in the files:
parts and their libraries:
wurth_electronics_midcom_inc_v1-0: Copyright: Wurth Electronics Midcom, Inc.
